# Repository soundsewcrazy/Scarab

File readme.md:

# Scarab

## Overview
Scarab is a custom input device that combines keyboard and trackball functionality into a single unit. It is designed for gaming and productivity use cases, with an emphasis on input control rather than traditional coding workflows. The device functions as a unified interface for both mouse and keyboard inputs, enabling gameplay in various environments.

> **Keyboard Maintainer**: [soundsewcrazy](https://github.com/soundsewcrazy)
> **Hardware Supported**: Pro Micro or clone hardware
> **Availability**: [GitHub releases](https://github.com/soundsewcrazy/Scarab/releases)

## Target Use Cases
- Gaming environments (RTS, MOBAs, FPS)
- Desktop workstations
- Portable use scenarios

The device is intended for users who require combined input methods in a single unit.

## 3D Files & Printing
- **Files Available**: STL files for all keyboard components are included in the repository for download and printing.
- **Recommended Printer**: ELEGOO Neptune 3 Plus (or compatible FDM printer).
- **Print Settings**: Use a 0.6mm nozzle with PETG filament.
- **Post-Processing**: Minor cleaning after printing is required to achieve proper fit with hardware and PCBs.
- **Model Tolerances**: Clearances are optimized for standard printers using a 0.6mm nozzle, resulting in a relatively tight fit.
- **Retention Mechanism**: Heat set inserts are used to secure components and hardware.
- **Keycap Requirement**: Regular keycaps will not fit due to the 16.5mm key spacing. Specific keycap models designed for this pitch must be used.

## PCB Information & Manufacture
- **Files Available**: PCB gerb files and original KiCad source are located in the `production` subfolder.
- **Manufacturing**: Initial runs were produced via JLCPCB (small quantities).
- **Switch Configuration**: Standard panels use regular Cherry MX switches. Akko Blue and Silver Speed switches are featured in documentation.
- **Switch Recommendations**: Linear switches are highly recommended for thumb clusters for easy actuation. Tactile or clicky switches may be used on hand panels if preferred.

## QMK Firmware & Keymapping
- **Firmware Tool**: QMK is required to compile firmware from source or flash precompiled HEX files.
- **Usage Methods**: 
  - Flash precompiled HEX files included in the repository.
  - Compile firmware directly from uncompiled source using QMK software.
- **Keymap Location**: Default keybindings are defined in the `keymaps` directory.
- **Customization Process**: 
  1. Edit keymap files within the `keymaps/` folder.
  2. Re-compile the firmware using QMK.
  3. Flash the updated HEX file to the device.

## Installation & Setup
- Clone the project from [GitHub](https://github.com/soundsewcrazy/Scarab).
- Install and configure QMK software on your machine.
- Select a firmware method (precompiled HEX or source compilation) based on technical preference.
- Initial configuration may require reference to variant documentation for keymap implementation.

## Variants
### Dynastinae — Thumb Support Model
The Dynastinae variant adds dedicated thumb panels to the standard trackball/keyboard hybrid. This configuration supports right-handed use as default, with left-handed assembly requiring component mirroring.

**Configuration:**
- Thumb Panels: 8 keys per cluster
- Hand Panels: Standard keyboard layout (30 keys, 5 rows of 6 columns)
- Left-Handed Assembly: Mirror body components to swap left/right panels

Additional variants are planned.

## Contributing & Community
Contributions through project forks are welcome

Support is community-driven; formal support is not guaranteed.
---
*This documentation reflects current information as of 2026-10-18.*

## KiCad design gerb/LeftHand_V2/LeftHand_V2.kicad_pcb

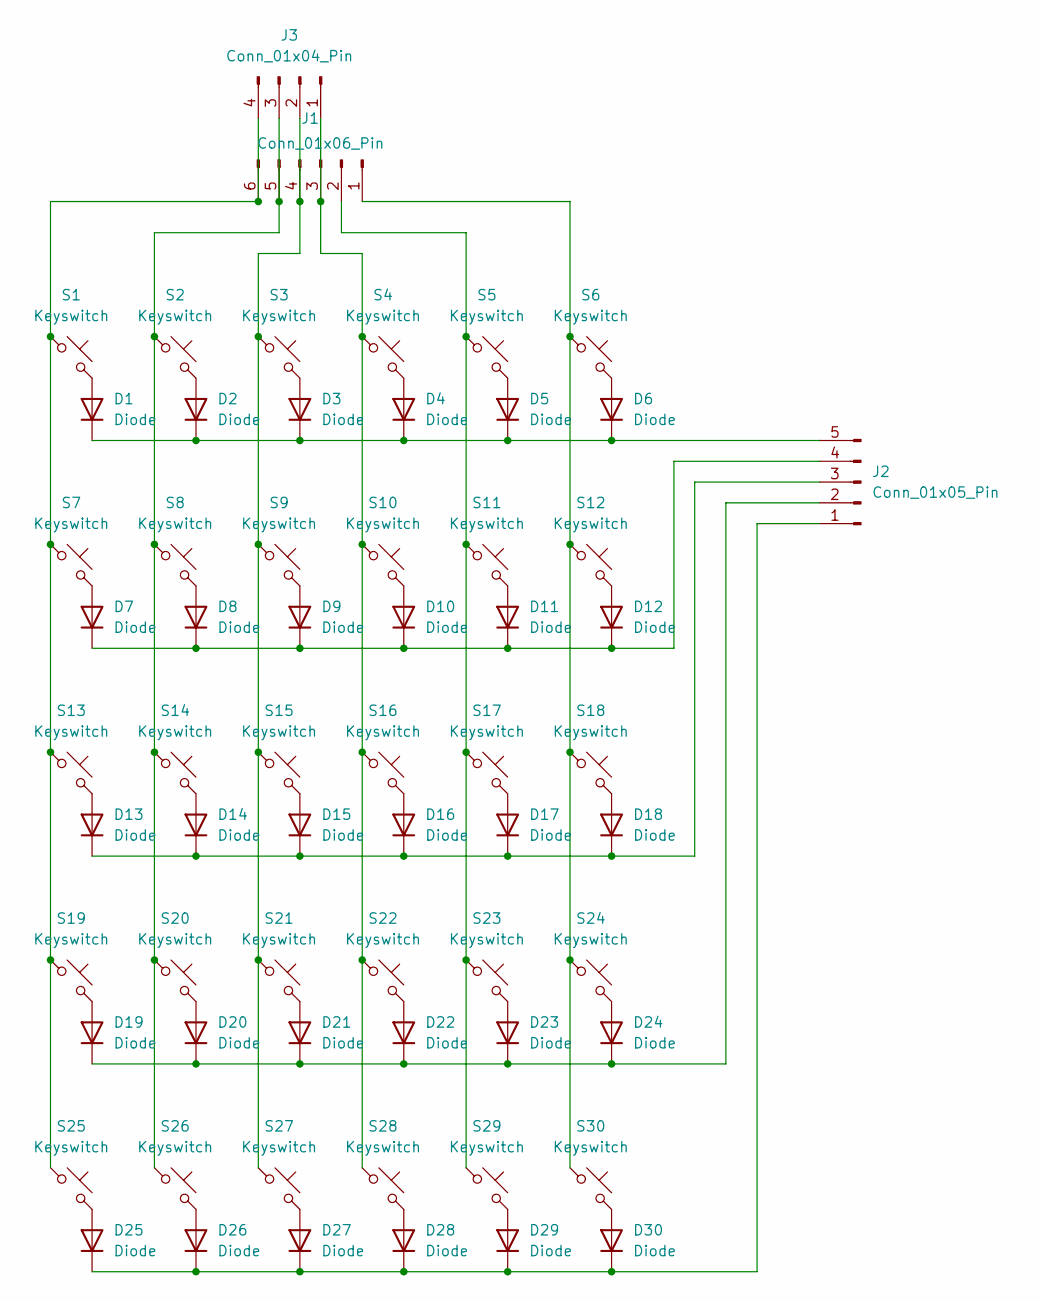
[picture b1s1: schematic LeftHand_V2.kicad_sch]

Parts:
D1, D2, D3, D4, D5, D6, D7, D8, D9, D10, D11, D12, D13, D14, D15, D16, D17, D18, D19, D20, D21, D22, D23, D24, D25, D26, D27, D28, D29, D30: Diode; Diode_DO-35
J1: Conn_01x06_Pin; PinHeader_1x06_P2.54mm_Vertical
J2: Conn_01x05_Pin; PinHeader_1x05_P2.54mm_Vertical
J3: Conn_01x04_Pin; PinHeader_1x04_P2.54mm_Vertical
S1, S2, S3, S4, S5, S6, S7, S8, S9, S10, S11, S12, S13, S14, S15, S16, S17, S18, S19, S20, S21, S22, S23, S24, S25, S26, S27, S28, S29, S30: Keyswitch; MX_PCB

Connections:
unnamed: D1.2 (A), S1.2
unnamed: D1.1 (K), D2.1 (K), D3.1 (K), D4.1 (K), D5.1 (K), D6.1 (K), J2.5
unnamed: D2.2 (A), S2.2
unnamed: D3.2 (A), S3.2
unnamed: D4.2 (A), S4.2
unnamed: D5.2 (A), S5.2
unnamed: D6.2 (A), S6.2
unnamed: D7.2 (A), S7.2
unnamed: D8.2 (A), S8.2
unnamed: D9.2 (A), S9.2
unnamed: D10.2 (A), S10.2
unnamed: D7.1 (K), D8.1 (K), D9.1 (K), D10.1 (K), D11.1 (K), D12.1 (K), J2.4
unnamed: D11.2 (A), S11.2
unnamed: D12.2 (A), S12.2
unnamed: D13.2 (A), S13.2
unnamed: D13.1 (K), D14.1 (K), D15.1 (K), D16.1 (K), D17.1 (K), D18.1 (K), J2.3
unnamed: D14.2 (A), S14.2
unnamed: D15.2 (A), S15.2
unnamed: D16.2 (A), S16.2
unnamed: D17.2 (A), S17.2
unnamed: D18.2 (A), S18.2
unnamed: D19.2 (A), S19.2
unnamed: D19.1 (K), D20.1 (K), D21.1 (K), D22.1 (K), D23.1 (K), D24.1 (K), J2.2
unnamed: D20.2 (A), S20.2
unnamed: D21.2 (A), S21.2
unnamed: D22.2 (A), S22.2
unnamed: D23.2 (A), S23.2
unnamed: D24.2 (A), S24.2
unnamed: D25.2 (A), S25.2
unnamed: D25.1 (K), D26.1 (K), D27.1 (K), D28.1 (K), D29.1 (K), D30.1 (K), J2.1
unnamed: D26.2 (A), S26.2
unnamed: D27.2 (A), S27.2
unnamed: D28.2 (A), S28.2
unnamed: D29.2 (A), S29.2
unnamed: D30.2 (A), S30.2
unnamed: J1.1, S6.1, S12.1, S18.1, S24.1, S30.1
unnamed: J1.2, S5.1, S11.1, S17.1, S23.1, S29.1
unnamed: J1.3, J3.1, S4.1, S10.1, S16.1, S22.1, S28.1
unnamed: J1.4, J3.2, S3.1, S9.1, S15.1, S21.1, S27.1
unnamed: J1.5, J3.3, S2.1, S8.1, S14.1, S20.1, S26.1
unnamed: J1.6, J3.4, S1.1, S7.1, S13.1, S19.1, S25.1

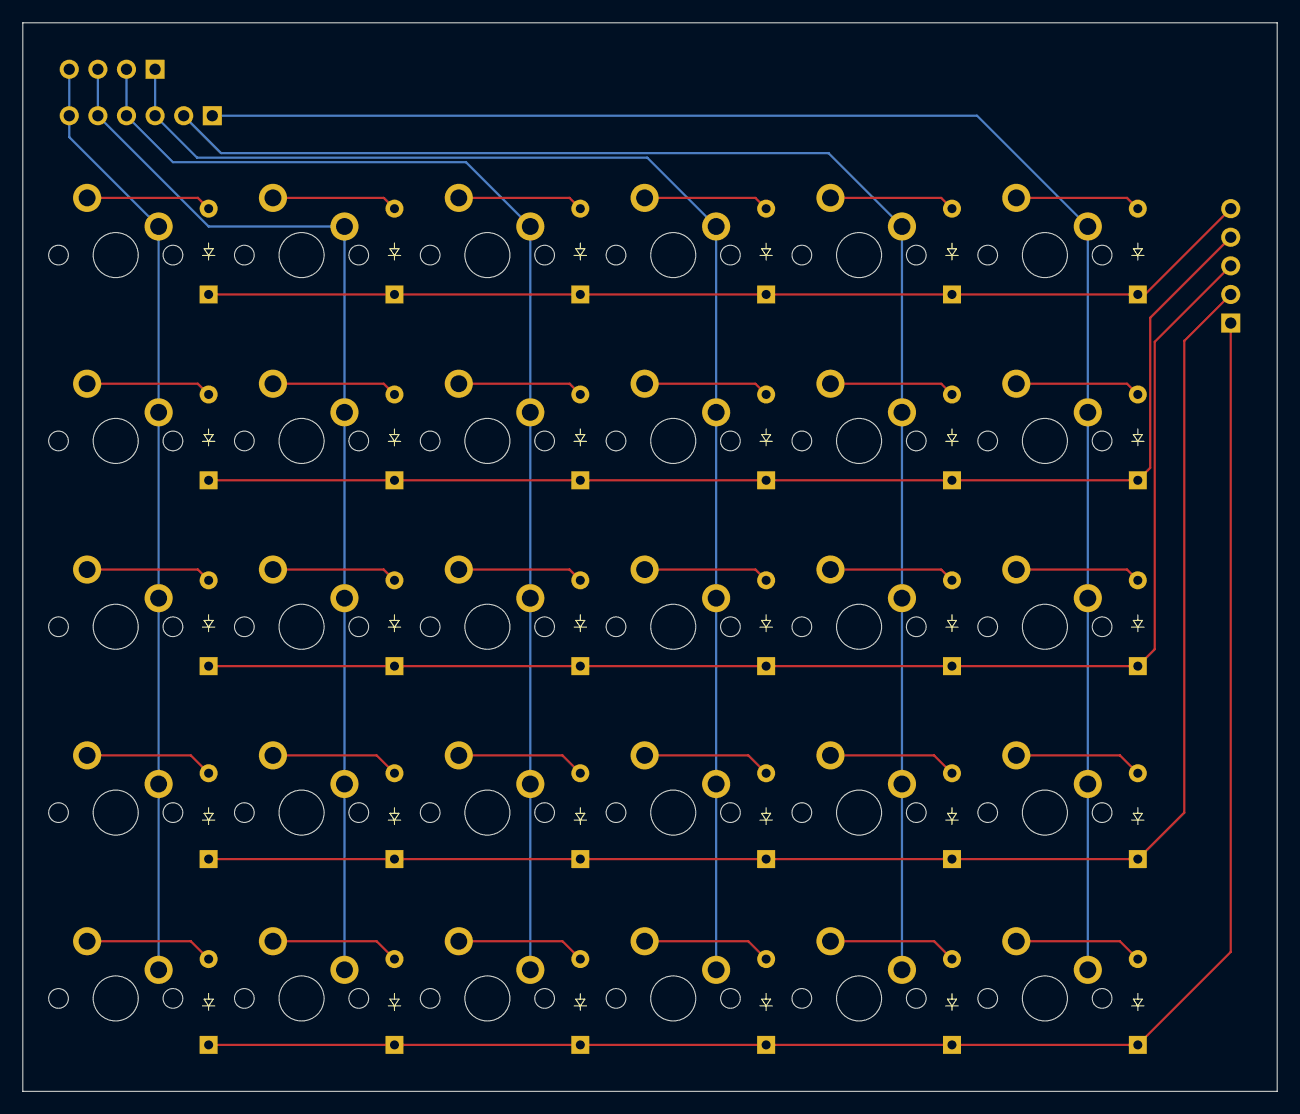
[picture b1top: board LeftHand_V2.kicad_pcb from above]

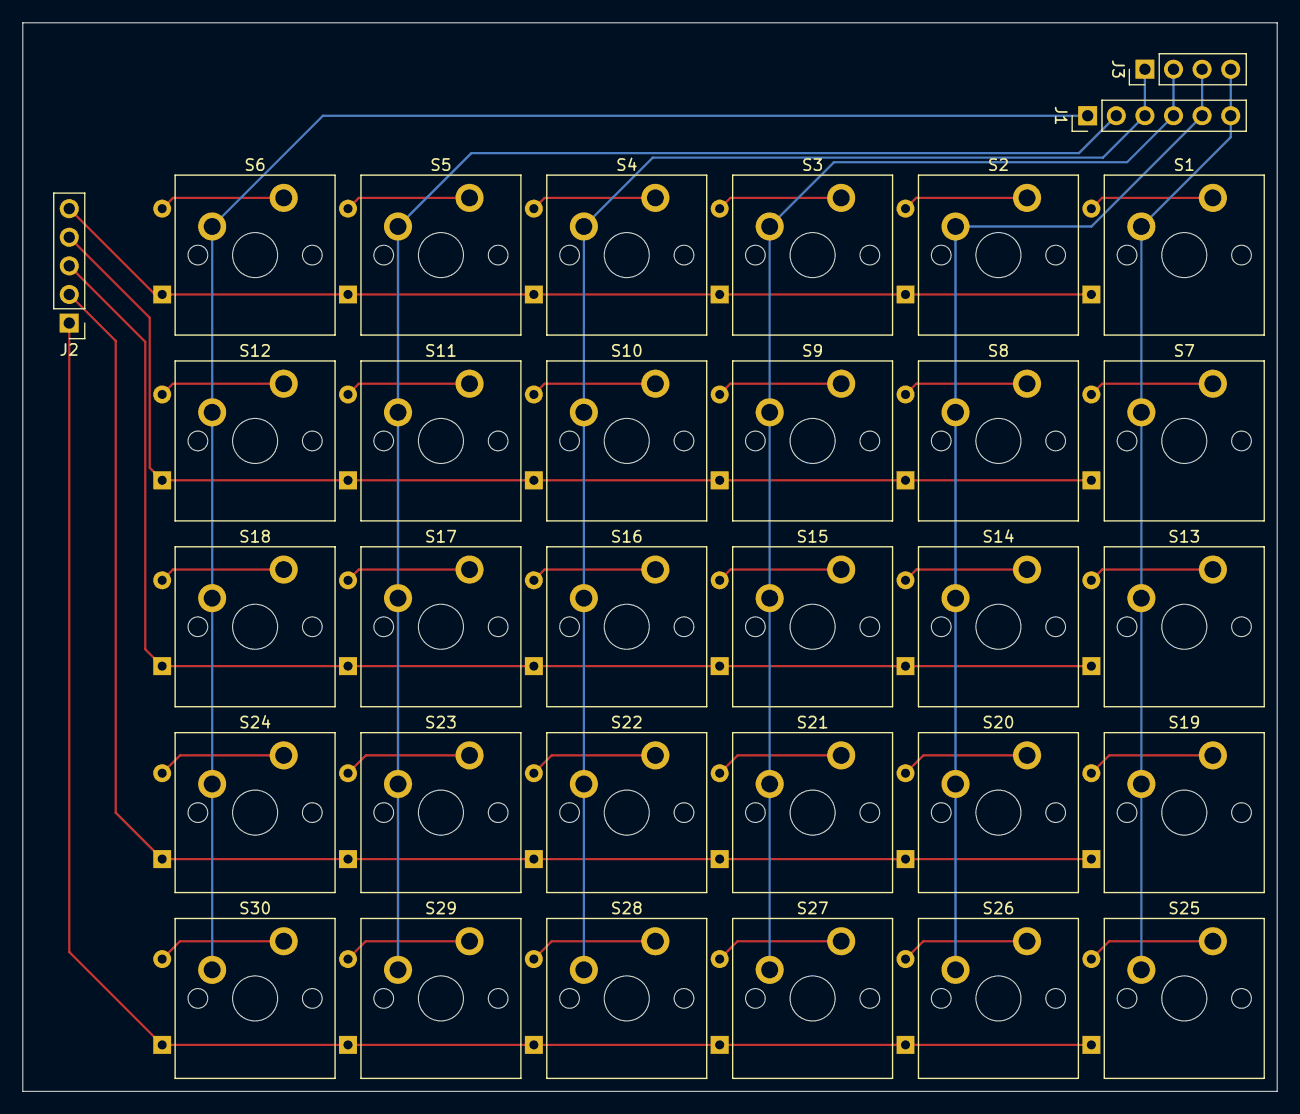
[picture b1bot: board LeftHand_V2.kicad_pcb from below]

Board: 2 copper layers, 111.4 x 94.9 mm, 63 parts (33 on the bottom side), 41 nets.

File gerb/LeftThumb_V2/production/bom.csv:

Designator,Footprint,Quantity,Value,LCSC Part #
"D1, D10, D2, D3, D4, D7, D8, D9",Diode_DO-35,8,Diode,
J1,PinHeader_1x02_P2.54mm_Vertical,1,Conn_01x02_Pin,
J3,PinHeader_1x04_P2.54mm_Vertical,1,Conn_01x04_Pin,
"S1, S10, S2, S3, S4, S7, S8, S9",MX_PCB,8,Keyswitch,
